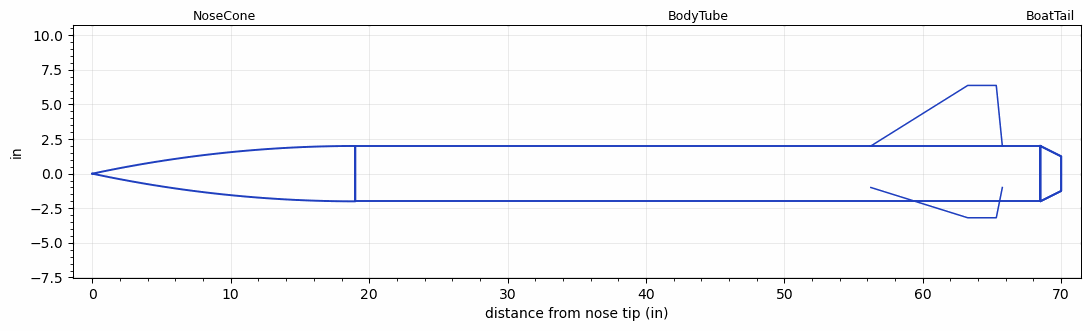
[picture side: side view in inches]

<RASAeroDocument>
 <FileVersion>2</FileVersion>
 <RocketDesign>
  <NoseCone>
   <Length>19</Length>
   <Diameter>4</Diameter>
   <Shape>Tangent Ogive</Shape>
   <Location>0</Location>
  </NoseCone>
  <BodyTube>
   <Length>49.5</Length>
   <Diameter>4</Diameter>
   <RailGuideDiameter>0.375</RailGuideDiameter>
   <RailGuideHeight>0.3438</RailGuideHeight>
   <Location>19</Location>
   <BoattailLength>1.5</BoattailLength>
   <BoattailRearDiameter>2.5</BoattailRearDiameter>
   <Fin>
    <Count>3</Count>
    <Chord>9.5</Chord>
    <Span>4.375</Span>
    <SweepDistance>7</SweepDistance>
    <TipChord>2.0625</TipChord>
    <Thickness>0.093</Thickness>
    <Location>12.25</Location>
    <AirfoilSection>Hexagonal</AirfoilSection>
    <FX1>0.75</FX1>
    <FX3>0.5</FX3>
   </Fin>
  </BodyTube>
  <BoatTail>
   <Length>1.5</Length>
   <Diameter>4</Diameter>
   <RearDiameter>2.5</RearDiameter>
   <Location>68.5</Location>
  </BoatTail>
  <Surface>Smooth (Zero Roughness)</Surface>
  <ModifiedBarrowman>False</ModifiedBarrowman>
  <Turbulence>False</Turbulence>
  <UseBooster1>False</UseBooster1>
  <UseBooster2>False</UseBooster2>
  <Comments>Ion Drive - Steve Sawyer
LDRS-26, Jean Dry Lake

Two Barometric Altimeters
AltAcc2 8302 ft
Perfect Flight 7752 ft
Average of Two Barometric Altimeters = 8027 ft

RASAero II Prediction = 8642 ft
Error = 7.66%
</Comments>
 </RocketDesign>
 <LaunchSite>
  <Altitude>2750</Altitude>
  <Pressure>0</Pressure>
  <RodAngle>0</RodAngle>
  <RodLength>10</RodLength>
  <Temperature>100</Temperature>
  <WindSpeed>0</WindSpeed>
 </LaunchSite>
 <Recovery>
  <Altitude1>1000</Altitude1>
  <Altitude2>1000</Altitude2>
  <Event1>False</Event1>
  <Event2>False</Event2>
  <Size1>1</Size1>
  <Size2>1</Size2>
  <EventType1>None</EventType1>
  <CD1>1.33</CD1>
  <CD2>1.33</CD2>
 </Recovery>
 <SimulationList>
  <Simulation>
   <SustainerEngine>K550W  (AT)</SustainerEngine>
   <SustainerLaunchWt>11.37</SustainerLaunchWt>
   <SustainerCG>39.5</SustainerCG>
   <SustainerIgnitionDelay>0</SustainerIgnitionDelay>
   <Booster1SeparationDelay>0</Booster1SeparationDelay>
   <Booster1IgnitionDelay>0</Booster1IgnitionDelay>
   <IncludeBooster1>False</IncludeBooster1>
   <Booster2Delay>0</Booster2Delay>
   <IncludeBooster2>False</IncludeBooster2>
   <TimetoApogee>21.90041</TimetoApogee>
   <MaxAltitude>8642.341</MaxAltitude>
   <MaxVelocity>926.7911</MaxVelocity>
  </Simulation>
 </SimulationList>
</RASAeroDocument>
